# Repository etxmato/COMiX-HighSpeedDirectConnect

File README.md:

# COMiX High Speed Direct Connect

With the High Speed Direct Connect HW & SW for the COMiX it is possible to transfer files between a modern PC and a COMiX. On the COMiX, PSAVE and PLOAD commands can be used with speeds of 9600 baud on a 2.8 Mhz CPU and 19200 baud on a 6 Mhz CPU.

Overview of the HSDC solution: 

Manual and all detailed information is available on our [Wiki](https://github.com/etxmato/COMiX-HighSpeedDirectConnect/wiki)

Andrew Wasson, 
Hank Riley,
Marcel van Tongeren

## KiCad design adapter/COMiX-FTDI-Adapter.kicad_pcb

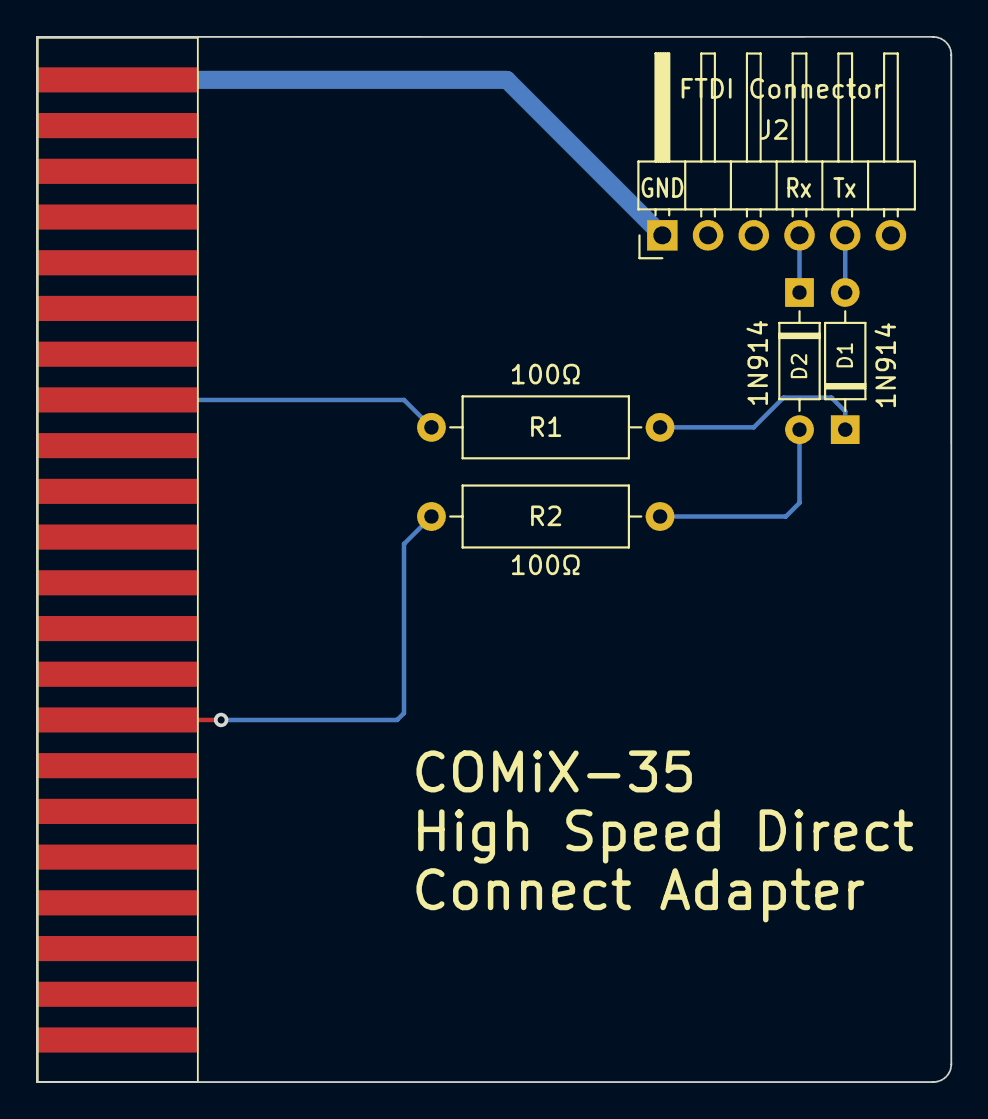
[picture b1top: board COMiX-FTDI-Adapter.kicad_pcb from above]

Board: 2 copper layers, 50.8 x 58.1 mm, 6 parts (0 on the bottom side), 7 nets.

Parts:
D1, D2: 1N914; D_DO-35_SOD27_P7.62mm_Horizontal
J1: EXPANSION; Edge_Card_Connector_22x2
J2: FTDI Connector; PinHeader_1x06_P2.54mm_Horizontal
R1, R2: 100Ω; R_Axial_DIN0309_L9.0mm_D3.2mm_P12.70mm_Horizontal

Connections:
/Q: J1.15 (pin), R1.1
/~EF4: J1.30, R2.1
GND: J1.1 (pin), J1.2, J2.1
unnamed: D1.2 (A), J2.5
unnamed: D1.1 (K), R1.2
unnamed: D2.2 (A), R2.2
unnamed: D2.1 (K), J2.4

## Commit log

2023-11-05 ad psave file for inspection
2023-11-18 add adapter card files
2023-11-18 add adapter scematic image
2023-11-20 Remove .DS_Store from current directory
2023-11-20 removed achived zips
2023-11-22 Original COMX FW
2023-11-22 Added original COMX FW versions
2023-11-26 Added overview picture
2023-11-26 ALt overview picture
2023-11-26 Changed to cropped overview
2023-11-29 Update README.md
    Restore original cropped system overview
2023-11-29 Update README.md
    New direct connect image
2023-11-30 update edge connector with curved edges
2023-11-30 Clean-up
2023-12-02 add adapter slim image, working files and gerbers
2023-12-02 add adapter smooth image
2023-12-06 add custom edge connector footprint
2023-12-11 New Edge Card PCB Images
2023-12-11 New Edge Card PCB Image
2023-12-11 Better Edge Card PCB Image
